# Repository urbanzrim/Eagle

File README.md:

# Eagle
Schematic, board and gerber files &amp; custom libraries

## Bluetooth sensor
42x32mm board with STM32l151, HC-05/06 and SHT21. 
Runs on one CR2032 battery.

## STM32f3 breakout board
Breakout board I made for quadcopter testing circuit.

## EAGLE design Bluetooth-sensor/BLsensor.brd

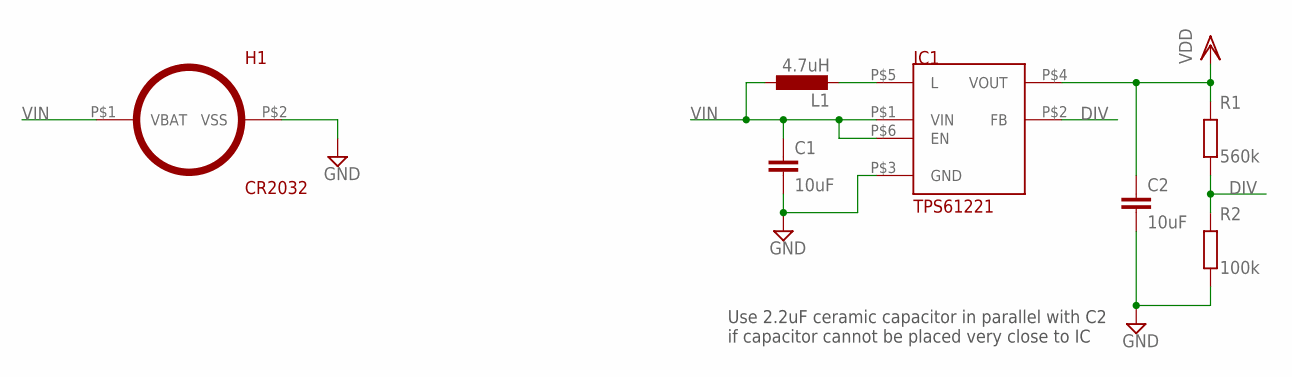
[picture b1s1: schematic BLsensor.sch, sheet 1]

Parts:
C1, C2: 10uF; C0402
H1: CR2032
IC1: TPS61221
L1: 4.7uH; L-EUC0402
R1: 560k; R0402
R2: 100k; R0402

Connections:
DIV: IC1.P$2 (FB), R1.2, R2.1
GND: C1.2, C2.2, H1.P$2 (VSS), IC1.P$3 (GND), R2.2; also elsewhere on the board
unnamed: IC1.P$5 (L), L1.P$2 (2)
VDD: C2.1, IC1.P$4 (VOUT), R1.1; also elsewhere on the board
VIN: C1.1, H1.P$1 (VBAT), IC1.P$1 (VIN), IC1.P$6 (EN), L1.P$1 (1)

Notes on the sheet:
Use 2.2uF ceramic capacitor in parallel with C2 if capacitor cannot be placed very close to IC

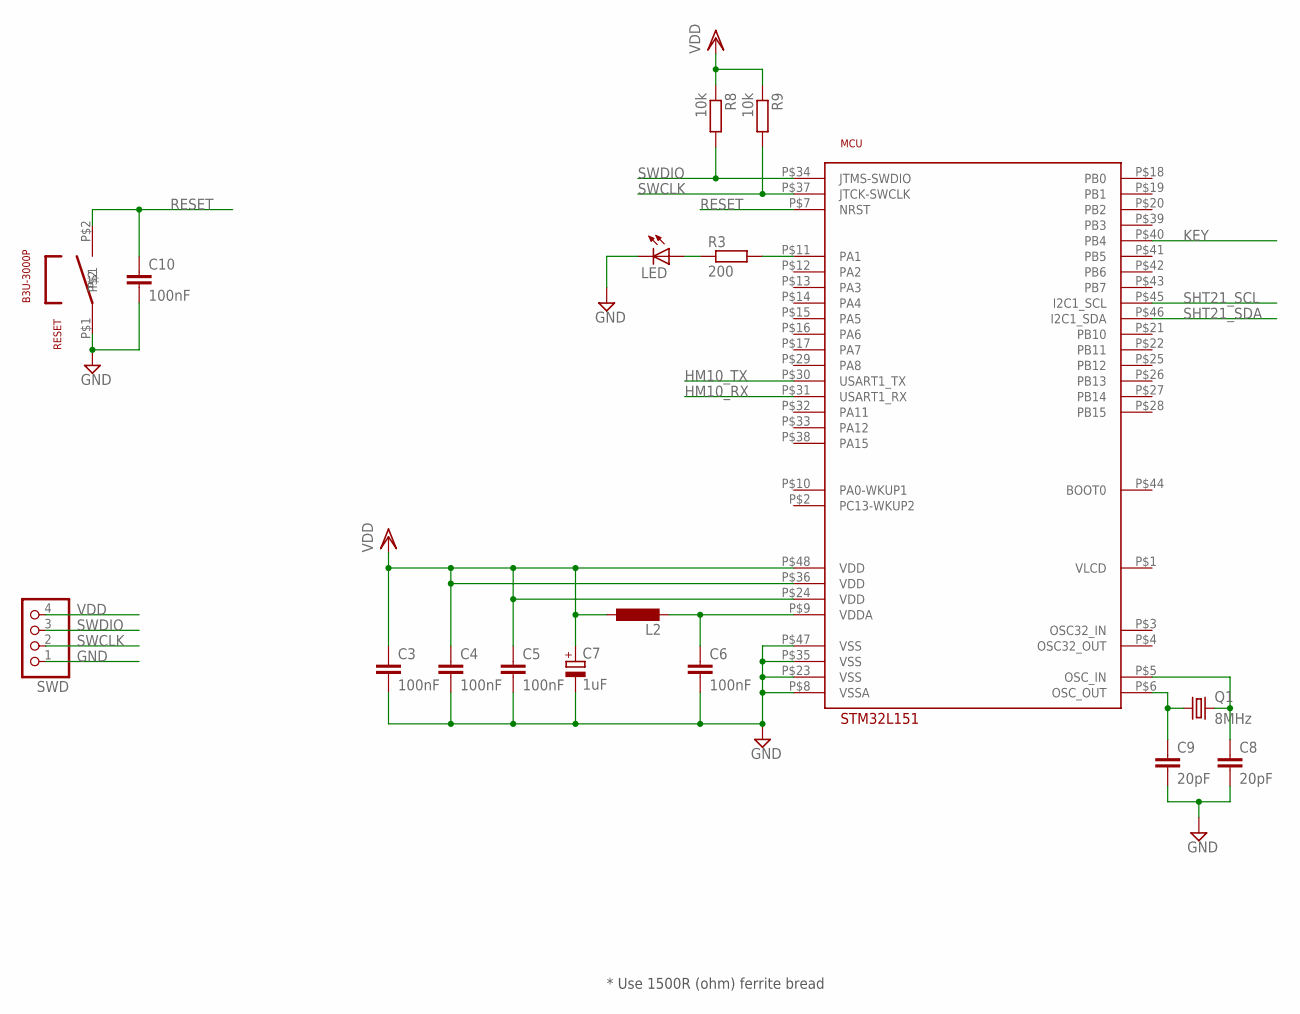
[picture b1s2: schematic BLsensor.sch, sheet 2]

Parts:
C3, C4, C5, C6, C10: 100nF; C0402
C7: 1uF; 153CRV
C8, C9: 20pF; C0402
L2: L-EU; L-EUC0402
LED: LEDCHIP-LED0603; CHIP-LED0603
MCU: STM32L151CC; STM32L151CCT6
Q1: 8MHz; ABM3
R3: 200; R0402
R8, R9: 10k; R0402
RESET: B3U-3000P
SWD: PINHD-1X4/90; 1X04/90

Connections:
GND: C3.2, C4.2, C5.2, C6.2, C7.P$1 (-), C8.2, C9.2, C10.2, LED.C, MCU.P$8 (VSSA), MCU.P$23 (VSS), MCU.P$35 (VSS), MCU.P$47 (VSS), RESET.P$1, SWD.1; also elsewhere on the board
HM10_RX: MCU.P$31 (USART1_RX); also elsewhere on the board
HM10_TX: MCU.P$30 (USART1_TX); also elsewhere on the board
KEY: MCU.P$40 (PB4); also elsewhere on the board
unnamed: C6.1, L2.P$2 (2), MCU.P$9 (VDDA)
unnamed: C9.1, MCU.P$6 (OSC_OUT), Q1.P$1 (1)
unnamed: C8.1, MCU.P$5 (OSC_IN), Q1.P$2 (2)
unnamed: MCU.P$11 (PA1), R3.2
unnamed: LED.A, R3.1
RESET: C10.1, MCU.P$7 (NRST), RESET.P$2
SHT21_SCL: MCU.P$45 (I2C1_SCL); also elsewhere on the board
SHT21_SDA: MCU.P$46 (I2C1_SDA); also elsewhere on the board
SWCLK: MCU.P$37 (JTCK-SWCLK), R9.2, SWD.2
SWDIO: MCU.P$34 (JTMS-SWDIO), R8.2, SWD.3
VDD: C3.1, C4.1, C5.1, C7.P$2 (+), L2.P$1 (1), MCU.P$24 (VDD), MCU.P$36 (VDD), MCU.P$48 (VDD), R8.1, R9.1, SWD.4; also elsewhere on the board

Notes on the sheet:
* Use 1500R (ohm) ferrite bread

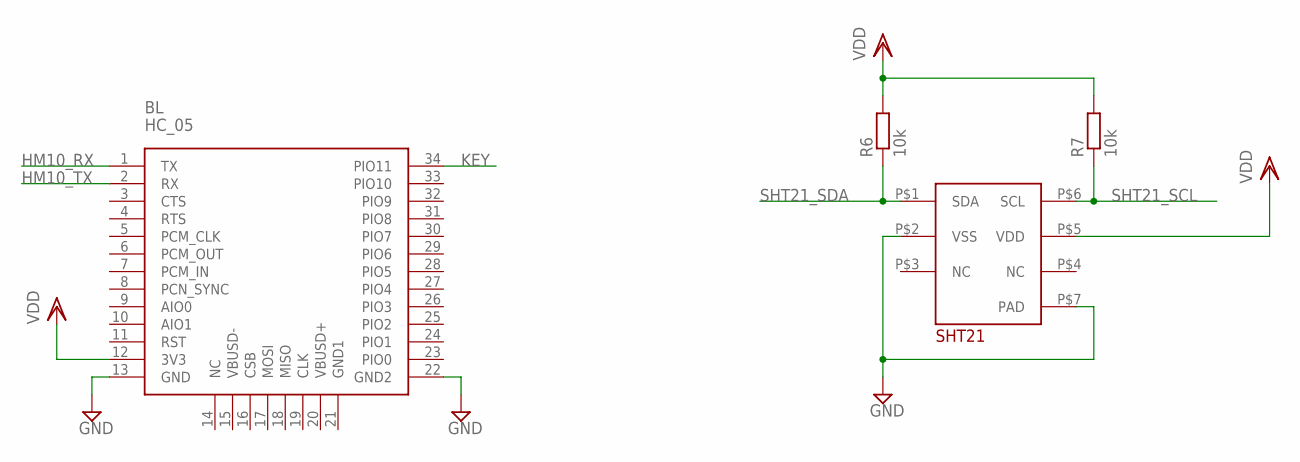
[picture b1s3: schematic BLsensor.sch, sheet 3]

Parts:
BL: HC_05; BLUETOOTH_SMD
R6, R7: 10k; R0402
U$1: SHT21

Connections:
GND: BL.13 (GND), BL.22 (GND2), U$1.P$2 (VSS), U$1.P$7 (PAD); also elsewhere on the board
HM10_RX: BL.1 (TX); also elsewhere on the board
HM10_TX: BL.2 (RX); also elsewhere on the board
KEY: BL.34 (PIO11); also elsewhere on the board
SHT21_SCL: R7.1, U$1.P$6 (SCL); also elsewhere on the board
SHT21_SDA: R6.1, U$1.P$1 (SDA); also elsewhere on the board
VDD: BL.12 (3V3), R6.2, R7.2, U$1.P$5 (VDD); also elsewhere on the board

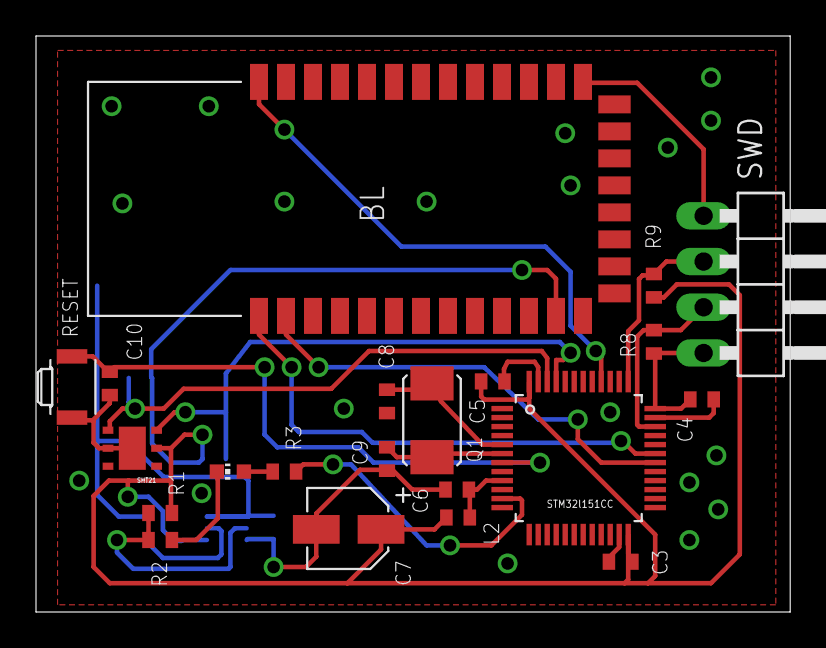
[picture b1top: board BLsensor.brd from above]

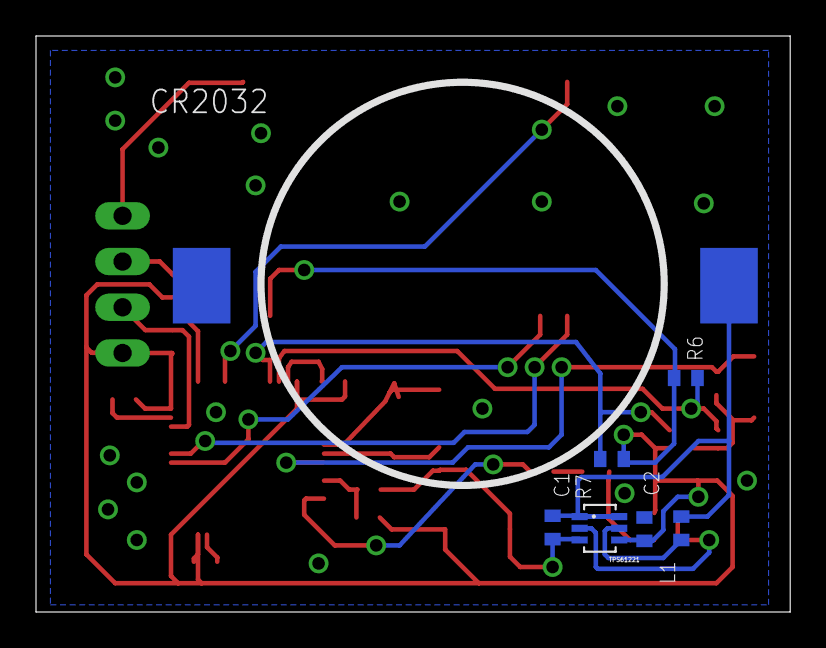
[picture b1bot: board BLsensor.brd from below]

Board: 2 copper layers, 41.9 x 32.0 mm, 28 parts (7 on the bottom side), 18 nets.

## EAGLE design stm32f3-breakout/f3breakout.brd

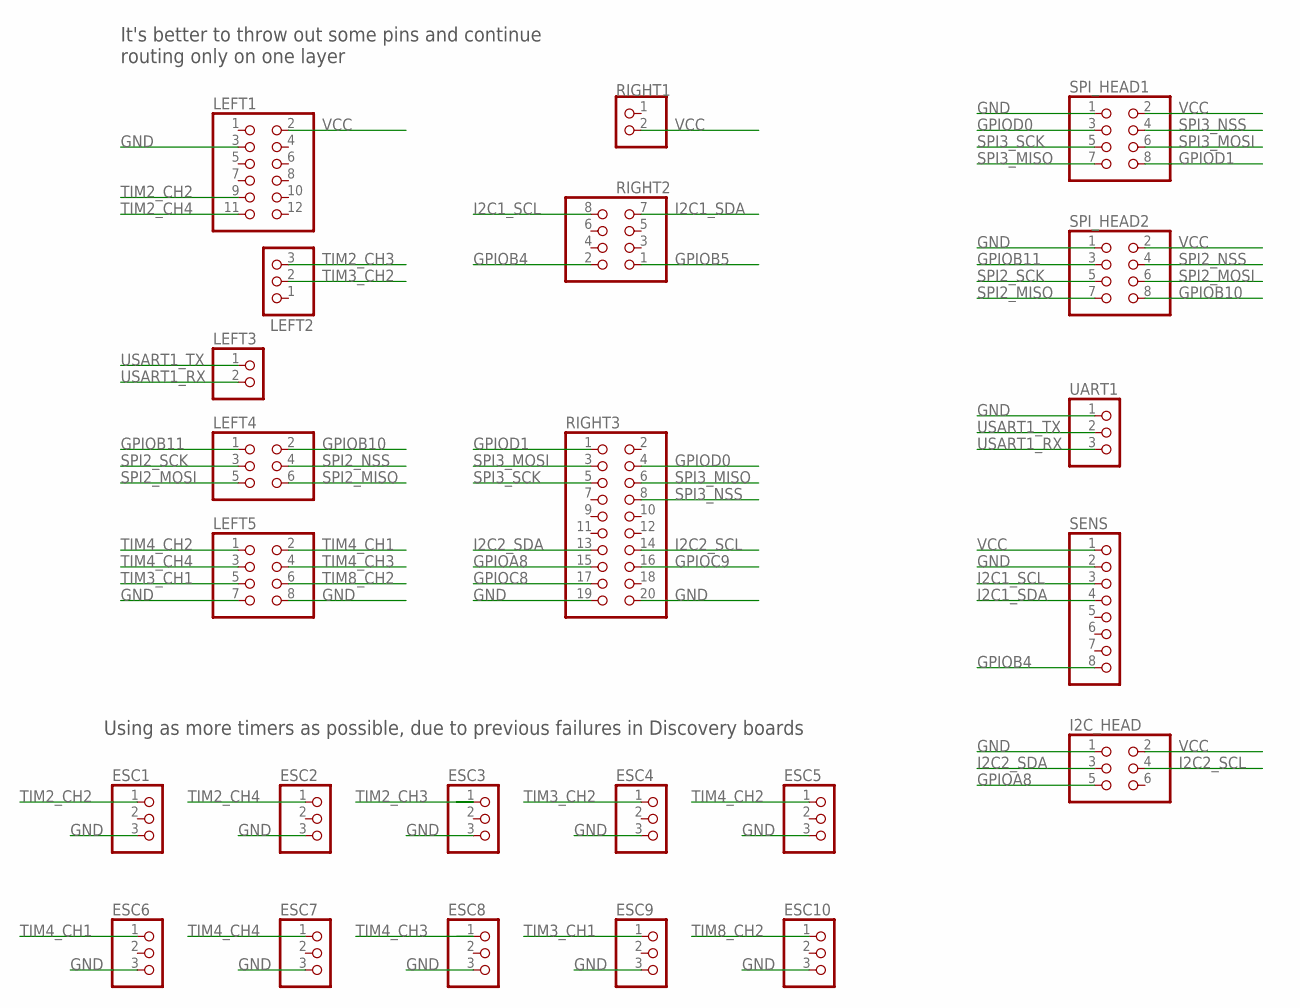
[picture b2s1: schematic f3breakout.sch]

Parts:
ESC1, ESC2, ESC3, ESC4, ESC5, ESC6, ESC7, ESC8, ESC9, ESC10: PINHD-1X3; 1X03
I2C_HEAD: PINHD-2X3; 2X03
LEFT1: PINHD-2X6; 2X06
LEFT2: PINHD-1X3; 1X03
LEFT3: PINHD-1X2; 1X02
LEFT4: PINHD-2X3; 2X03
LEFT5: PINHD-2X4; 2X04
RIGHT1: PINHD-1X2; 1X02
RIGHT2: PINHD-2X4; 2X04
RIGHT3: PINHD-2X10; 2X10
SENS: PINHD-1X8; 1X08
SPI_HEAD1, SPI_HEAD2: PINHD-2X4; 2X04
UART1: PINHD-1X3; 1X03

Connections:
GND: ESC1.3, ESC2.3, ESC3.3, ESC4.3, ESC5.3, ESC6.3, ESC7.3, ESC8.3, ESC9.3, ESC10.3, I2C_HEAD.1, LEFT1.3, LEFT5.7, LEFT5.8, RIGHT3.19, RIGHT3.20, SENS.2, SPI_HEAD1.1, SPI_HEAD2.1, UART1.1
GPIOA8: I2C_HEAD.5, RIGHT3.15
GPIOB4: RIGHT2.2, SENS.8
GPIOB5: RIGHT2.1
GPIOB10: LEFT4.2, SPI_HEAD2.8
GPIOB11: LEFT4.1, SPI_HEAD2.3
GPIOC8: RIGHT3.17
GPIOC9: RIGHT3.16
GPIOD0: RIGHT3.4, SPI_HEAD1.3
GPIOD1: RIGHT3.1, SPI_HEAD1.8
I2C1_SCL: RIGHT2.8, SENS.3
I2C1_SDA: RIGHT2.7, SENS.4
I2C2_SCL: I2C_HEAD.4, RIGHT3.14
I2C2_SDA: I2C_HEAD.3, RIGHT3.13
SPI2_MISO: LEFT4.6, SPI_HEAD2.7
SPI2_MOSI: LEFT4.5, SPI_HEAD2.6
SPI2_NSS: LEFT4.4, SPI_HEAD2.4
SPI2_SCK: LEFT4.3, SPI_HEAD2.5
SPI3_MISO: RIGHT3.6, SPI_HEAD1.7
SPI3_MOSI: RIGHT3.3, SPI_HEAD1.6
SPI3_NSS: RIGHT3.8, SPI_HEAD1.4
SPI3_SCK: RIGHT3.5, SPI_HEAD1.5
TIM2_CH2: ESC1.1, LEFT1.9
TIM2_CH3: ESC3.1, LEFT2.3
TIM2_CH4: ESC2.1, LEFT1.11
TIM3_CH1: ESC9.1, LEFT5.5
TIM3_CH2: ESC4.1, LEFT2.2
TIM4_CH1: ESC6.1, LEFT5.2
TIM4_CH2: ESC5.1, LEFT5.1
TIM4_CH3: ESC8.1, LEFT5.4
TIM4_CH4: ESC7.1, LEFT5.3
TIM8_CH2: ESC10.1, LEFT5.6
USART1_RX: LEFT3.2, UART1.3
USART1_TX: LEFT3.1, UART1.2
VCC: I2C_HEAD.2, LEFT1.2, RIGHT1.2, SENS.1, SPI_HEAD1.2, SPI_HEAD2.2

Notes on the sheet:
Using as more timers as possible, due to previous failures in Discovery boards
It's better to throw out some pins and continue routing only on one layer

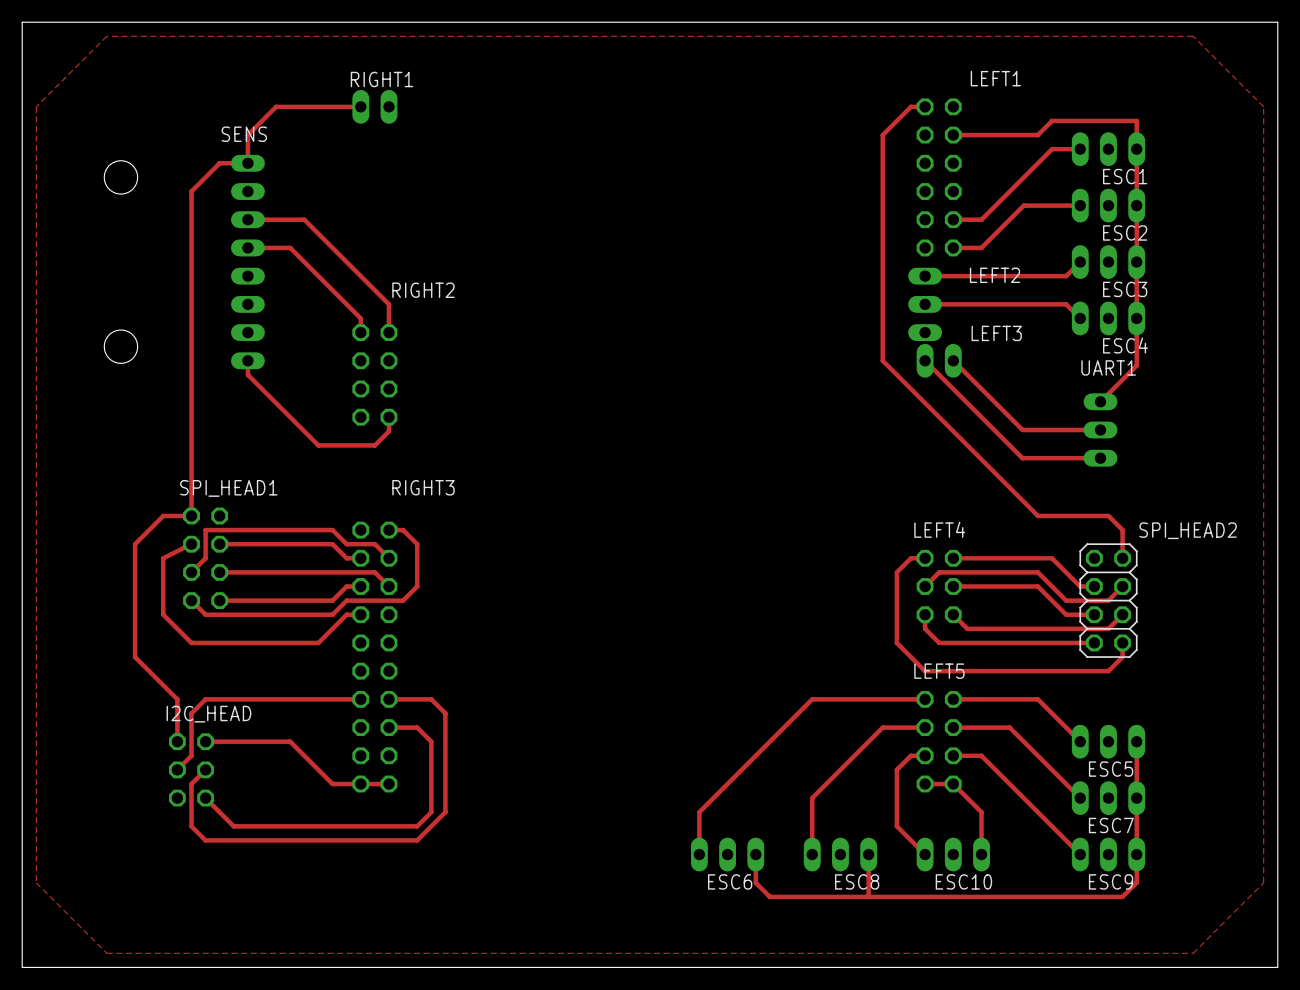
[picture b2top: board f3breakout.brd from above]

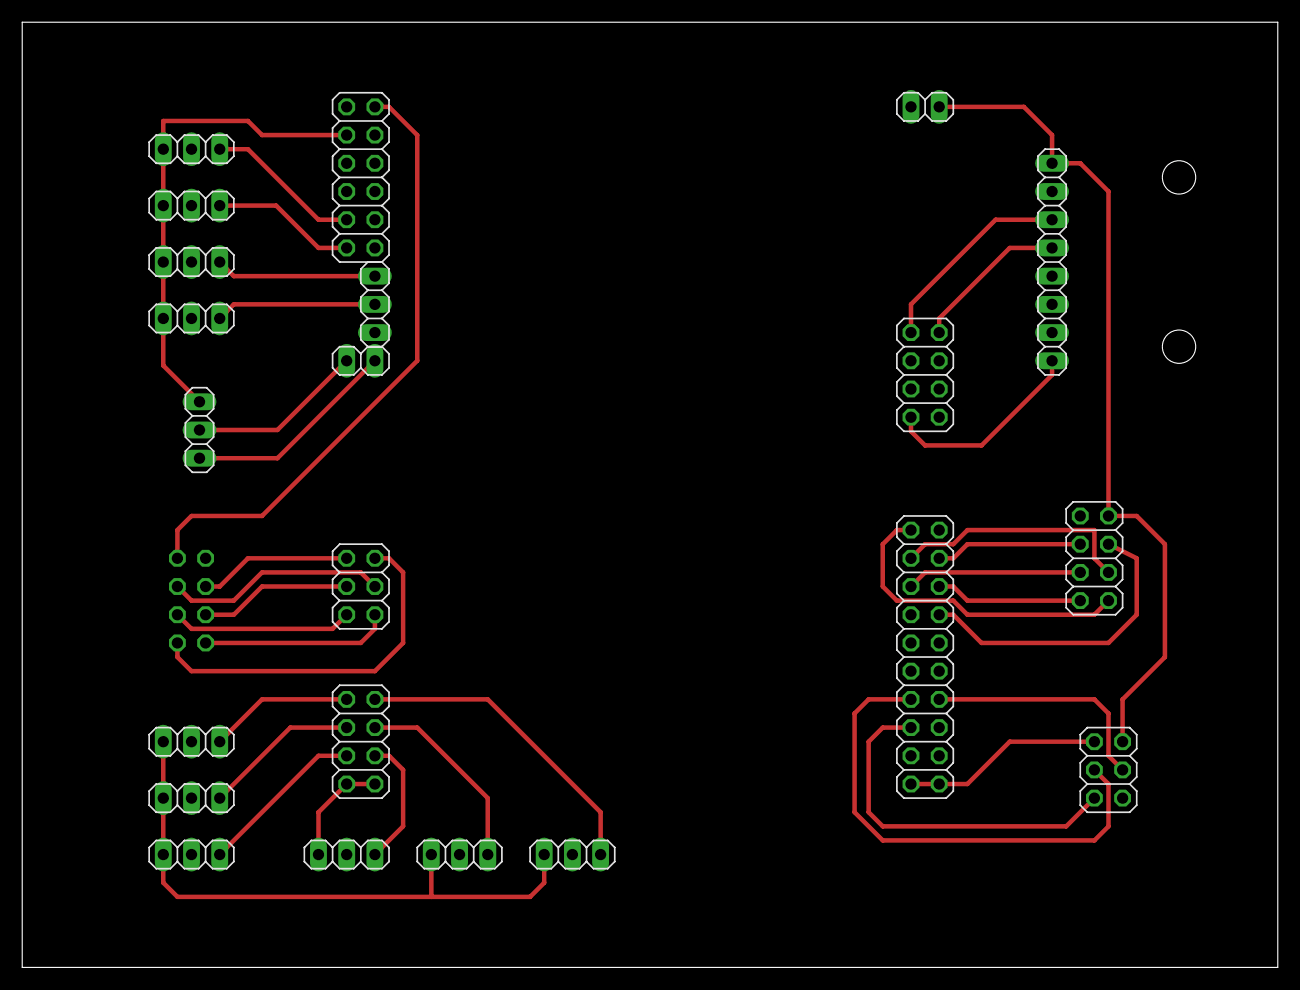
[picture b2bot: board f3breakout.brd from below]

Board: 2 copper layers, 113.0 x 85.1 mm, 23 parts (22 on the bottom side), 32 nets.

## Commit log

2015-04-06 :tada: Added .gitattributes & .gitignore files
2015-04-15 Added new lib
2015-06-27 Board and sch for bl sensor
    Schematic and board layout for low power bluetooth sensor
2015-06-27 new lib
2015-09-25 Created Readme
2017-02-20 Library for stm32f303 series
    first commit with f303VCT6
2017-02-23 LIS2DH accelerometer
2017-02-23 mpl3115a2 pressure sensor
